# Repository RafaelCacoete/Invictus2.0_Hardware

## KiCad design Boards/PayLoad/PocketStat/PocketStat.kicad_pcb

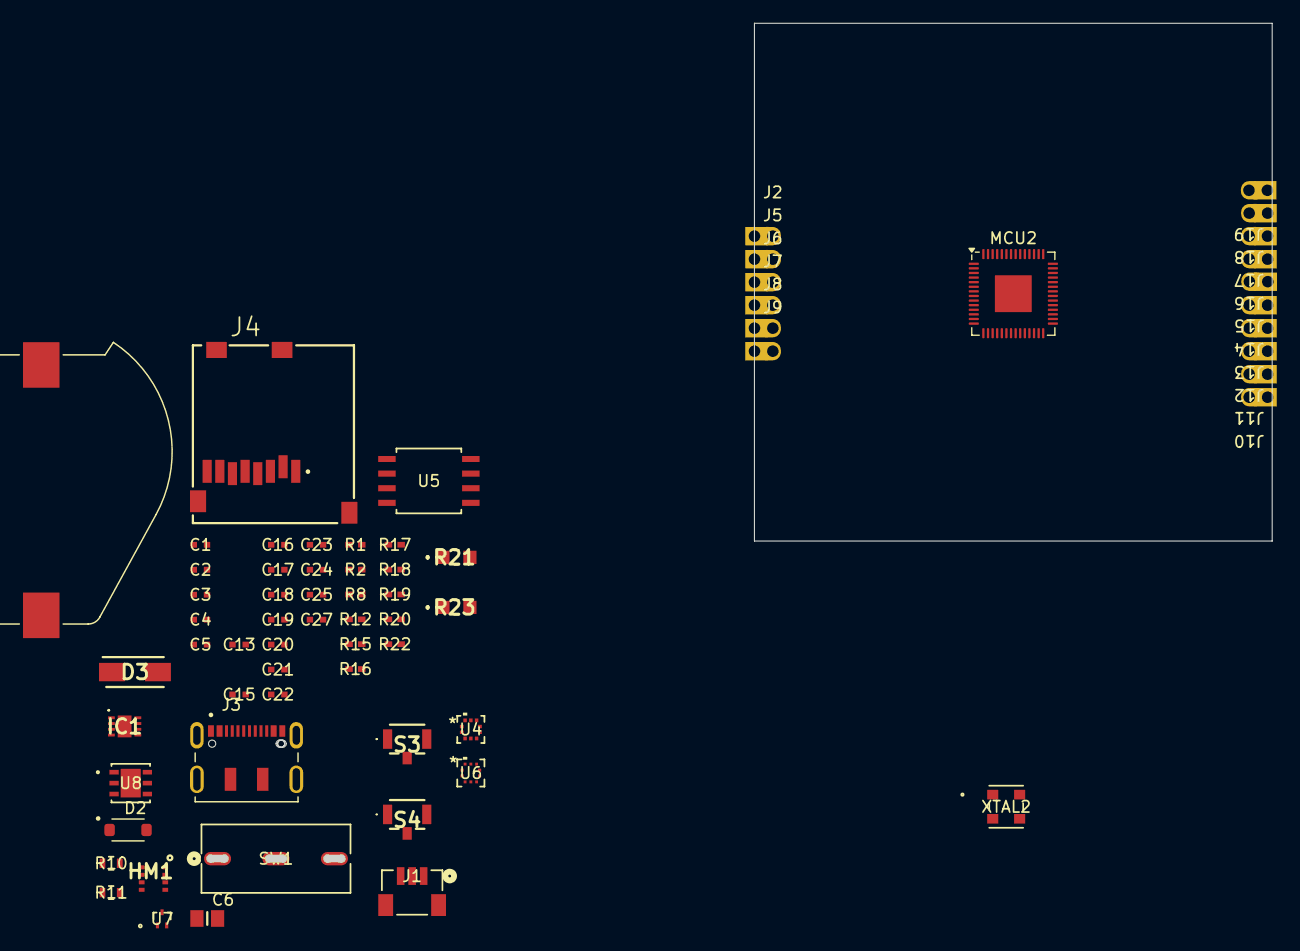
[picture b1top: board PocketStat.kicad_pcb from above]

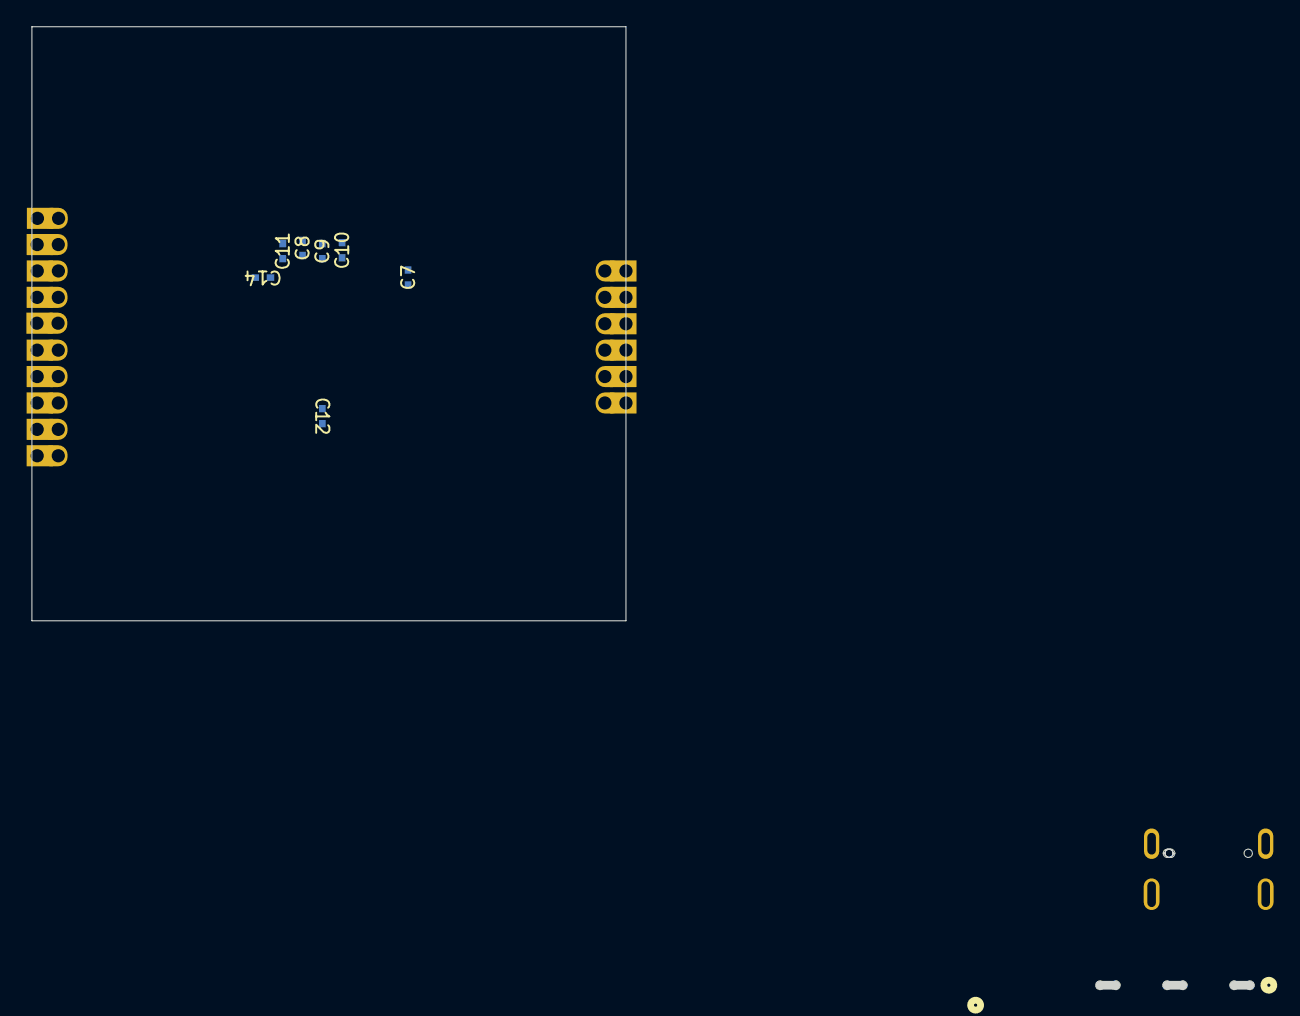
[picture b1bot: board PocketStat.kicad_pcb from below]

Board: 4 copper layers, 92.3 x 72.6 mm, 75 parts (7 on the bottom side), 59 nets, no tracks yet.

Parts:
BT1: 1062TR; BAT_1062TR
C1, C2, C3, C13: 100nF; Capacitor_0402
C4, C5, C7, C9, C10, C11, C12, C14, C15, C16, C17, C19, C21, C27: 100n; Capacitor_0402
C6: 10u; Capacitor_0805
C8: 1uF; Capacitor_0402
C18, C20, C24, C25: 1u; Capacitor_0402
C22, C23: 4.7u; Capacitor_0402
D2: PMEG2010ER; SODFL3517X110N
D3: RSX301L; DIOM5026X220N
HM1: BME280
IC1: HDC3022QDEJRQ1
J1: BM03B-SRSS-TBLFSN; CONN_BM03B-SRSS-TBLFSN_JST
J2, J5, J6, J7, J8, J9, J10, J11, J12, J13, J14, J15, J16, J17, J18, J19: Conn_01x01_Socket; Pico_01pin
J3: DX07S016JA1R1500; JAE_DX07S016JA1R1500
J4: MEM2061-01-188-00-A_REVA; GCT_MEM2061-01-188-00-A_REVA
MCU2: RP2040; QFN-56-1EP_7x7mm_P0.4mm_EP3.2x3.2mm
R1, R2, R17, R18: 2k; RES_0402
R8, R16, R22: 1k; RES_0402
R10, R11: 27; RES_0603
R12, R15: 100; RES_0402
R19, R20: 10k; RES_0402
R21, R23: 5k1; RES_0805
S3, S4: TL1017AABF160QG
SW1: D2F-01-D; D2F-01-D_OMR
U4: LPS22DFTR; QFN_22DFTR_STM
U5: W25Q128JVSIQ TR; SOIC_208MIL_WIN
U6: BMP581; QFN10_BMP581_BOS
U7: ESD7L5.0DT5G; SOT-723_0P85X1P25_ONS
U8: ST1L05APU33R; DFN_5APU33R_STM
XTAL2: ASE-12.000MHZ-LC-T; ASE-3.2X2.5_ABR

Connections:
+3.3V: C1.2, C2.2, C3.1, C4.2, C5.2, C6.1, C7.1, C8.1, C9.1, C10.1, C11.1, C12.1, C13.2, C14.1, C15.1, C16.1, C21.1, C23.2, C25.1, C27.2, HM1.2 (CSB), HM1.6 (VDDIO), HM1.8 (VDD), IC1.5 (VDD), IC1.6 (~RESET), J4.4 (VDD), MCU2.1 (IOVDD), MCU2.10 (IOVDD), MCU2.22 (IOVDD), MCU2.33 (IOVDD), MCU2.42 (IOVDD), MCU2.43 (ADC_AVDD), MCU2.44 (VREG_IN), MCU2.48 (USB_VDD), MCU2.49 (IOVDD), R1.1, R2.1, R8.1, R17.1, R18.1, R19.2, U4.1 (Vdd_IO), U4.10 (VDD), U5.8 (VCC), U6.1 (VDDIO), U6.10 (VDD), U8.2 (V0), XTAL2.4 (VDD)
/BAR1 ~CS: MCU2.12 (GPIO9), U4.6 (CS)
/BAR1_RDY: MCU2.8 (GPIO6), U4.7 (INT_DRDY)
/BAR2 RDY: MCU2.9 (GPIO7), U6.7 (INT)
/BAR2 ~CS: MCU2.16 (GPIO13), U6.6 (CSB)
/Crystal: MCU2.20 (XIN), XTAL2.3 (OUTPUT)
/Humidity ALERT: MCU2.15 (GPIO12), R20.1
/MCU QSPI_SCLK: MCU2.52 (QSPI_SCLK), U5.6 (CLK)
/MCU QSPI_SD0: MCU2.53 (QSPI_SD0), U5.5 (DI(IO0))
/MCU QSPI_SD1: MCU2.55 (QSPI_SD1), U5.2 (DO(IO1))
/MCU QSPI_SD2: MCU2.54 (QSPI_SD2), U5.3 (/WP(IO2))
/MCU QSPI_SD3: MCU2.51 (QSPI_SD3), U5.7 (/HOLD_/RESET)
/MCU QSPI_SS: MCU2.56 (QSPI_SS), R22.2, U5.1 (/CS)
/SCL I2C: HM1.4 (SCK), IC1.4 (SCL), MCU2.18 (GPIO15), R2.2, R17.2
/SD-Card SPI MISO: J4.7 (DAT0), MCU2.27 (GPIO16)
/SD-Card SPI MOSI: J4.3 (CMD), MCU2.30 (GPIO19)
/SD-Card SPI SCK: J4.5 (CLK), MCU2.29 (GPIO18)
/SD-Card SPI ~CS: J4.2 (CD/DAT3), MCU2.28 (GPIO17)
/SDA I2C: HM1.3 (SDI), IC1.1 (SDA), MCU2.17 (GPIO14), R1.2, R18.2
/SPI1_MISO: MCU2.11 (GPIO8), U4.5 (SDO/SA0), U6.5 (SDO)
/SPI1_MOSI: MCU2.14 (GPIO11), U4.4 (SDA/SDI/SDISDO), U6.4 (SDI)
/SPI1_SCK: MCU2.13 (GPIO10), U4.2 (SCK), U6.2 (SCK)
/USB_DM: J3.5 (D-), J3.8 (D-), R11.1, U7.1
/USB_DP: J3.6 (D+), J3.7 (D+), R10.1, U7.2
/~RST: R16.1, S3.2 (NO)
GND: BT1.N, C1.1, C2.1, C3.2, C4.1, C5.1, C6.2, C7.2, C8.2, C9.2, C10.2, C11.2, C12.2, C13.1, C14.2, C15.2, C16.2, C17.1, C18.2, C19.1, C20.2, C21.2, C22.1, C23.1, C24.1, C25.2, C27.1, HM1.1 (GND_1), HM1.5 (SDO), HM1.7 (GND_2), IC1.2 (ADDR), IC1.7 (ADDR1), IC1.8 (GND), IC1.9 (EP), J1.2, J3.1 (GND), J3.12 (GND), J4.6 (VSS), J4.9 (CD1), J4.10 (CD2), J4.11 (GND), J4.12 (GND), MCU2.19 (TESTEN), MCU2.57 (GND), R21.1, R23.1, S3.1 (COM), S3.G1, S4.1 (COM), S4.G1, U4.3 (RES), U4.8 (GND_IO), U4.9 (GND), U5.4 (GND), U6.3 (VSS), U6.8 (VSS), U6.9 (VSS), U7.3, U8.6 (GND), U8.7 (GND), XTAL2.2 (GND/CASE)
unnamed: BT1.P, SW1.3
unnamed: D2.A, SW1.1
unnamed: D3.2 (A), J3.2 (VBUS), J3.11 (VBUS)
unnamed: IC1.3 (ALERT), R20.2
unnamed: J1.1, R12.1
unnamed: J1.3, R15.1
unnamed: J2.1, MCU2.2 (GPIO0)
unnamed: J3.3 (CC1), R21.2
unnamed: J3.9 (CC2), R23.2
unnamed: J5.1, MCU2.3 (GPIO1)
unnamed: J6.1, MCU2.4 (GPIO2)
unnamed: J7.1, MCU2.5 (GPIO3)
unnamed: J8.1, MCU2.6 (GPIO4)
unnamed: J9.1, MCU2.7 (GPIO5)
unnamed: J10.1, MCU2.31 (GPIO20)
unnamed: J11.1, MCU2.32 (GPIO21)
unnamed: J12.1, MCU2.34 (GPIO22)
unnamed: J13.1, MCU2.35 (GPIO23)
unnamed: J14.1, MCU2.36 (GPIO24)
unnamed: J15.1, MCU2.37 (GPIO25)
unnamed: J16.1, MCU2.38 (GPIO26_ADC0)
unnamed: J17.1, MCU2.39 (GPIO27_ADC1)
unnamed: J18.1, MCU2.40 (GPIO28_ADC2)
unnamed: J19.1, MCU2.41 (GPIO29_ADC3)
unnamed: C20.1, MCU2.26 (RUN), R8.2, R16.2
unnamed: MCU2.24 (SWCLK), R12.2
unnamed: MCU2.25 (SWD), R15.2
unnamed: MCU2.46 (USB_DM), R11.2
unnamed: MCU2.47 (USB_DP), R10.2
unnamed: C17.2, C18.1, C19.2, MCU2.23 (DVDD), MCU2.45 (VREG_VOUT), MCU2.50 (DVDD)
unnamed: R22.1, S4.2 (NO)
unnamed: R19.1, XTAL2.1 (TRI-STATE(STBY))
VBUS: C22.2, C24.2, D2.C, D3.1 (K), U8.3 (V1)

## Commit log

2025-03-07 Recomecei o PCB da Pocket Stat
